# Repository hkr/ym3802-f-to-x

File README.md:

# ym3802-f-to-x
Adapter to use the YM3802-F SMD component as YM3802-X DIP40

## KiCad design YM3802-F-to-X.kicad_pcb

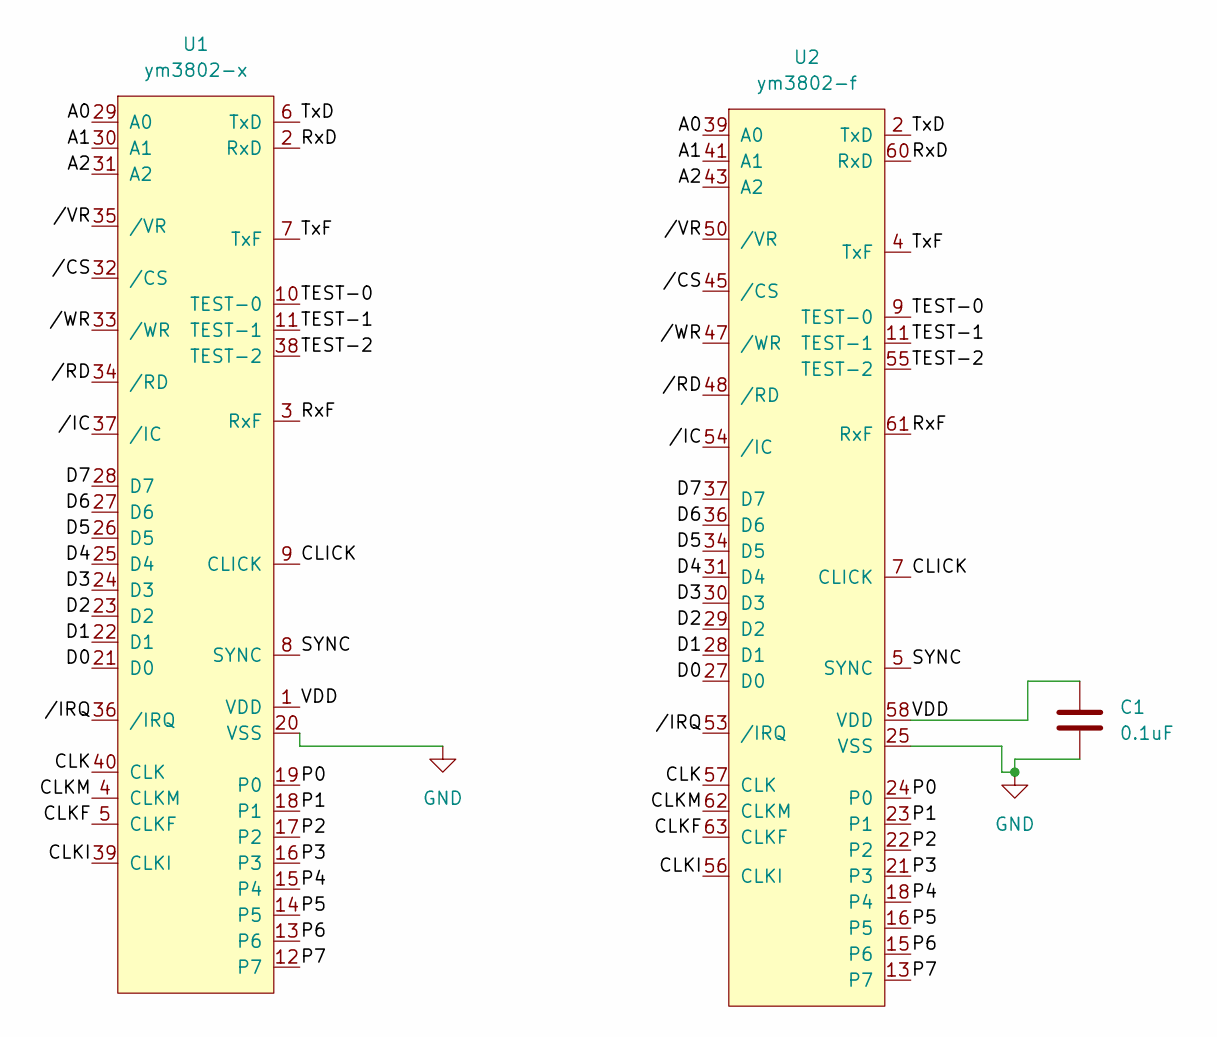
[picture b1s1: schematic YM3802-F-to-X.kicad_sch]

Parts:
C1: 0.1uF; C_0805_2012Metric_Pad1.18x1.45mm_HandSolder
U1: ym3802-x; preci-dip-150-10-640-00-106161_2x20_P2.54mm_Vertical_SMD
U2: ym3802-f; YM3802-F

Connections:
/A0: U1.29 (A0), U2.39 (A0)
/A1: U1.30 (A1), U2.41 (A1)
/A2: U1.31 (A2), U2.43 (A2)
/CLICK: U1.9 (CLICK), U2.7 (CLICK)
/CLK: U1.40 (CLK), U2.57 (CLK)
/CLKF: U1.5 (CLKF), U2.63 (CLKF)
/CLKI: U1.39 (CLKI), U2.56 (CLKI)
/CLKM: U1.4 (CLKM), U2.62 (CLKM)
/D0: U1.21 (D0), U2.27 (D0)
/D1: U1.22 (D1), U2.28 (D1)
/D2: U1.23 (D2), U2.29 (D2)
/D3: U1.24 (D3), U2.30 (D3)
/D4: U1.25 (D4), U2.31 (D4)
/D5: U1.26 (D5), U2.34 (D5)
/D6: U1.27 (D6), U2.36 (D6)
/D7: U1.28 (D7), U2.37 (D7)
/P0: U1.19 (P0), U2.24 (P0)
/P1: U1.18 (P1), U2.23 (P1)
/P2: U1.17 (P2), U2.22 (P2)
/P3: U1.16 (P3), U2.21 (P3)
/P4: U1.15 (P4), U2.18 (P4)
/P5: U1.14 (P5), U2.16 (P5)
/P6: U1.13 (P6), U2.15 (P6)
/P7: U1.12 (P7), U2.13 (P7)
/RxD: U1.2 (RxD), U2.60 (RxD)
/RxF: U1.3 (RxF), U2.61 (RxF)
/SYNC: U1.8 (SYNC), U2.5 (SYNC)
/TEST-0: U1.10 (TEST-0), U2.9 (TEST-0)
/TEST-1: U1.11 (TEST-1), U2.11 (TEST-1)
/TEST-2: U1.38 (TEST-2), U2.55 (TEST-2)
/TxD: U1.6 (TxD), U2.2 (TxD)
/TxF: U1.7 (TxF), U2.4 (TxF)
/VDD: C1.1, U1.1 (VDD), U2.58 (VDD)
//CS: U1.32 (/CS), U2.45 (/CS)
//IC: U1.37 (/IC), U2.54 (/IC)
//IRQ: U1.36 (/IRQ), U2.53 (/IRQ)
//RD: U1.34 (/RD), U2.48 (/RD)
//VR: U1.35 (/VR), U2.50 (/VR)
//WR: U1.33 (/WR), U2.47 (/WR)
GND: C1.2, U1.20 (VSS), U2.25 (VSS)

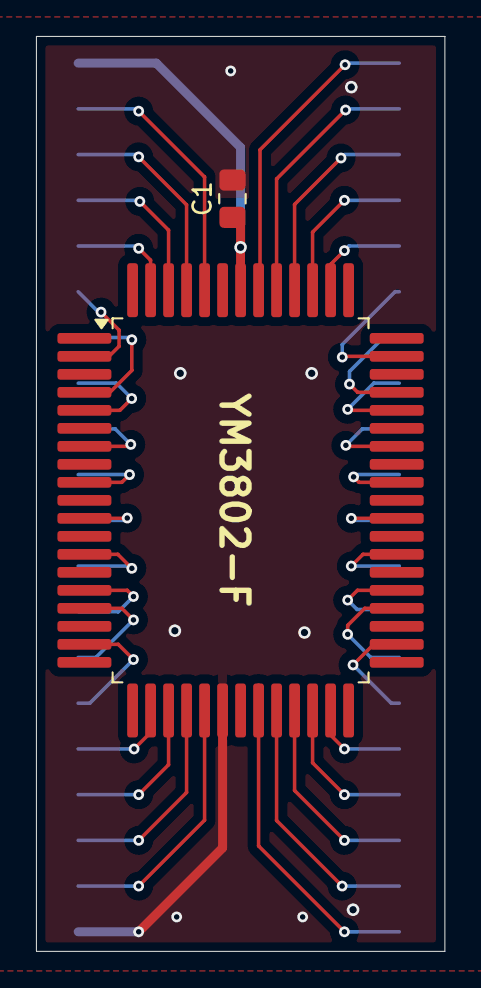
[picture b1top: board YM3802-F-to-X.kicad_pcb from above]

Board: 2 copper layers, 22.7 x 50.8 mm, 3 parts (1 on the bottom side), 40 nets.

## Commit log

2025-03-20 Initial version
2025-03-20 Add photo
